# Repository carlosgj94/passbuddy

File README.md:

# Passbuddy — Hardware KeePass for ESP32-S3

Passbuddy is a no_std Rust firmware for the ESP32-S3 that acts like a USB keyboard (HID) to auto-type passwords stored in an on-device KeePass database. The database lives in flash and is encrypted with a software key derived from a user PIN plus the chip’s efuse keyslot 0 (unreadable externally), so secrets never leave the device.

## How It Works
- **Key derivation:** User PIN + IFUSE/HMAC using keyslot 0 → one-time KDF output (software key). The hardware root key never leaves the chip, and the PIN never leaves the device. The software key encrypts/decrypts the KeePass DB.
- **Usage model:** Plug the device; it enumerates as a USB keyboard. Enter PIN locally (buttons/rotary/etc). The DB decrypts on-device. When a login field is focused, the device types the selected password over USB keystrokes.
- **Security posture:** No cloud or sync. Flash theft is useless without the PIN and bypassing S3 anti-dump protections. Vendor compromise is irrelevant because secrets stay on hardware.

## Project Layout
- `src/bin/main.rs` — ESP-RTOS entrypoint; sets CPU clocks, HMAC peripheral, SPI2, and SSD1309 display; draws a simple `ratatui` list via `mousefood`; logs a heartbeat.
- `src/display.rs` — display helpers (`init_terminal`, `initial_state`, `draw_menu`).
- `src/display/ssd1309.rs` — SSD1309 SPI driver implementing `embedded-graphics` `DrawTarget` + framebuffer flush.
- `src/encryption.rs` — HMAC-based software key derivation (`derive_sw_key`).
- `build.rs` — adds linker scripts (`defmt.x`, `linkall.x`) and prints hints for missing symbols.
- `.cargo/config.toml` — targets `xtensa-esp32s3-none-elf`, sets `espflash` runner, enables `build-std` for `core`/`alloc`.

## Prereqs
- Rust toolchain channel `esp` (see `rust-toolchain.toml`); install Xtensa support via Espressif’s toolchain (e.g., `espup`).
- `espflash` installed and USB permissions set (dialout/uaccess on Linux).

## Build, Flash, and Dev
```bash
cargo build                 # dev build for ESP32-S3
cargo build --release       # size-optimized
cargo clippy --no-deps      # lint; keep warnings at zero
cargo run                   # flash + defmt monitor via espflash (device attached)
```
Notes: ensure only one serial/monitor session is open when flashing; replug USB if flashing stalls.

## Architecture Notes
- No_std + Embassy executor; heap set via `esp_alloc::heap_allocator!` in `main`.
- Display: SSD1309 over SPI2 (custom driver); UI rendered with `ratatui`/`mousefood`.
- HID keyboard output planned for password typing; input hardware for PIN entry is TBD.

## Status / Next Steps
- ✅ Display init and static menu render.
- ✅ Software key derivation helper using HMAC + RNG.
- ⏳ Implement PIN input, KeePass DB storage/crypto flow, HID keyboard typing, and runtime UI updates (via Embassy task).

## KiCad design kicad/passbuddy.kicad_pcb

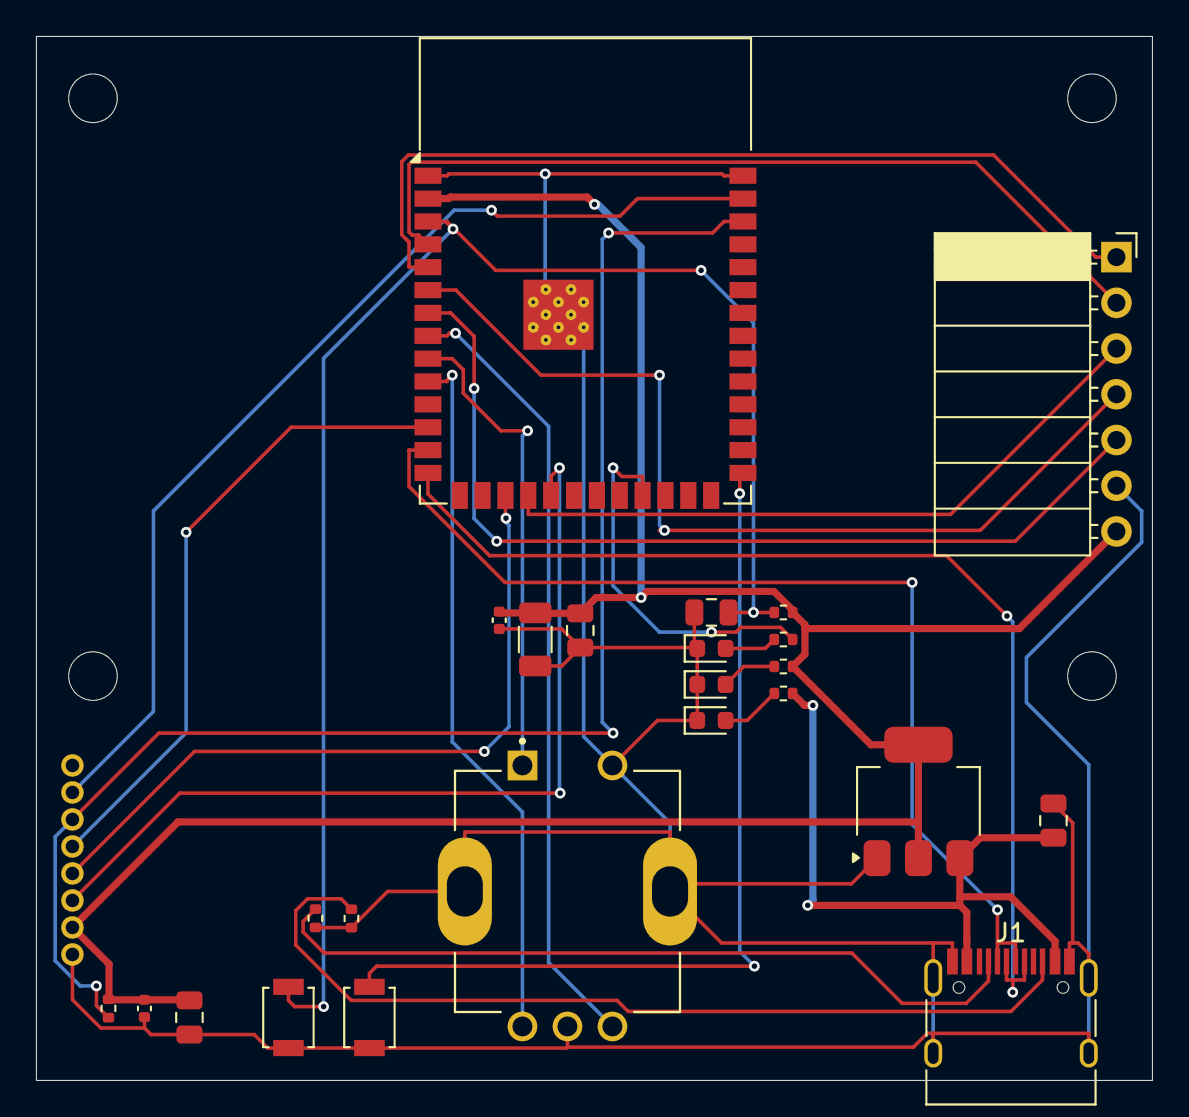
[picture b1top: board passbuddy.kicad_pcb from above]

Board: 2 copper layers, 62.0 x 58.0 mm, 29 parts (0 on the bottom side), 26 nets.

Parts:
C1, C4, C5: 10uF 0805; C_0805_2012Metric
C2: 22uF 1206; C_1206_3216Metric
C3, C6: 100nF 0402; C_0402_1005Metric
C7: 4.7uF 0805; C_0805_2012Metric
D1, D2, D3: LED 0603 White; LED_0603_1608Metric
J1: USB_C_Receptacle_USB2.0_16P; USB_C_Receptacle_HRO_TYPE-C-31-M-12
J2: Conn_01x08_Socket; Tropic01_PinSocket
J3: Conn_01x07_Pin; PinSocket_1x07_P2.54mm_Horizontal
MountHole1, MountHole3, MountHole4: MountHole; MountingHole_2.7mm_M2.5
MountHole2: MountingHole_2.7mm_M2.5
R1, R2, R3, R4, R5, R6: 5.1kΩ 0402; R_0402_1005Metric
R7: 10kΩ 0402; R_0402_1005Metric
S1: PEC11R-4220F-S0024; XDCR_PEC11R-4220F-S0024
SW2, SW3: SW_SPST; SW_SPST_B3U-1000P
U1: ESP32-S3-WROOM-1
U2: LD1117S33TR_SOT223; SOT-223-3_TabPin2

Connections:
+3V3: C1.1, C2.1, C3.1, C6.1, C7.1, J2.7, J3.7, R4.2, R6.1, R7.2, U1.2 (3V3), U2.2 (VO)
+5V: C4.1, J1.A4 (VBUS), J1.A9 (VBUS), J1.B4 (VBUS), J1.B9 (VBUS), R5.1, U2.3 (VI)
CLK: J3.4, U1.6 (IO6)
CS: J3.3, U1.18 (IO10)
D+: J1.A6 (D+), J1.B6 (D+), U1.14 (USB_D+)
D-: J1.A7 (D-), J1.B7 (D-), U1.13 (USB_D-)
DC: J3.2, U1.4 (IO4)
DIN: J3.5, U1.7 (IO7)
EN: C5.1, R6.2, SW3.2 (B), U1.3 (EN)
GND: C1.2, C2.2, C3.2, C4.2, C5.2, C6.2, C7.2, D1.1 (K), D2.1 (K), D3.1 (K), J1.A1 (GND), J1.A12 (GND), J1.B1 (GND), J1.B12 (GND), J1.S1 (SHIELD), J2.8, J3.6, R1.2, R2.2, S1.2, S1.C (COM), S1.SH1 (SHIELD), S1.SH2 (SHIELD), SW2.1 (A), SW3.1 (A), U1.1 (GND), U1.40 (GND), U1.41 (GND), U2.1 (GND)
GPIO0: SW2.2 (B), U1.27 (IO0)
GPIO16: S1.1, U1.9 (IO16)
GPIO21: R3.1, U1.23 (IO21)
unnamed: D1.2 (A), R5.2
unnamed: D2.2 (A), R4.1
unnamed: D3.2 (A), R3.2
unnamed: J1.A5 (CC1), R1.1
unnamed: J1.B5 (CC2), R2.1
RST: J3.1, U1.5 (IO5)
RT_CLK: S1.A, U1.10 (IO17)
RT_DT: S1.B, U1.8 (IO15)
TROPIC_CLK: J2.4, U1.12 (IO8)
TROPIC_CS: J2.3, R7.1, U1.38 (IO2)
TROPIC_GPO: J2.2, U1.39 (IO1)
TROPIC_SDI: J2.6, U1.19 (IO11)
TROPIC_SDO: J2.5, U1.17 (IO9)

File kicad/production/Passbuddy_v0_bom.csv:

Designator,Footprint,Quantity,Value,LCSC Part #
"C1, C4, C5",0805,3,10uF 0805,
C2,1206,1,22uF 1206,
"C3, C6",0402,2,100nF 0402,
C7,0805,1,4.7uF 0805,
"D1, D2, D3",0603,3,LED 0603 White,
J1,USB_C_Receptacle_HRO_TYPE-C-31-M-12,1,USB_C_Receptacle_USB2.0_16P,C53207138
J2,Tropic01_PinSocket,1,Conn_01x08_Socket,
J3,PinSocket_1x07_P2.54mm_Horizontal,1,Conn_01x07_Pin,C2897389
"R1, R2, R3, R4, R5, R6",0402,6,5.1kΩ 0402,
R7,0402,1,10kΩ 0402,
S1,XDCR_PEC11R-4220F-S0024,1,PEC11R-4220F-S0024,
"SW2, SW3",SW_SPST_B3U-1000P,2,SW_SPST,C720477
U1,ESP32-S3-WROOM-1,1,ESP32-S3-WROOM-1,C2913202
U2,SOT-223-3_TabPin2,1,LD1117S33TR_SOT223,C6186

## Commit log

2025-12-10 feat: initial commit
2025-12-10 feat: adding the encryption module with its first function
2025-12-10 feat: adding the initial logic for the display
2025-12-10 chore: adding agents.md
2025-12-10 chore: refactored the display functionality
2025-12-10 feat: added the readme
2025-12-10 chore: removing unneeded no_std
2025-12-10 feat: adding the parsing of the headers for keepass
2025-12-11 feat: adding the entry struct for keepass v1
2025-12-11 feat: adding the group struct
2025-12-11 feat: adding the db
2025-12-11 feat: adding the readme for the keepass database file structure
2025-12-11 feat: adding the dma helper for usage on the key generation
2025-12-11 feat: init structs for the storage module
2025-12-11 feat: storage refactor and adding a function to get the offset to the user storage
2025-12-11 feat: added more metadata in the layout
2025-12-11 feat: initializing the OS storage readying
2025-12-11 feat: starting to hook the layout with main
2025-12-12 feat: setting up the storage write up on first boot
2025-12-12 feat: removing writes from read functions
2025-12-12 feat: magic/offset bug
2025-12-12 feat: making the size of the storage layout constant
2025-12-12 fix: keepass types missalignment
2025-12-12 fix: more fixes on the types for the keepass db
2025-12-12 chore: adding logs to check the OS is working correctly
2025-12-12 fix: avoiding busy spining
2025-12-12 feat: starting the kpdb read
2025-12-13 fix: removing the long ass vec
2025-12-13 feat: adding the ssd1309 driver and hooking it up to the tui
2025-12-13 feat: adding the potentiometer as an input
2025-12-13 feat: refactoring a bit the ui and creating the action button in the inputs
2025-12-13 feat: adding more views to the app
2025-12-13 feat: refactoring the state adding it into the AppState
2025-12-14 feat: refactoring the whole app state and rendering of screens
2025-12-15 feat: adding the group decoding and readying
2025-12-15 feat: loading up the keepass ram db
2025-12-15 feat: adding the display of the different groups in the screens and major refactors in the screens
2025-12-16 fix: offset layout and various errors preventing initialization
2025-12-16 feat: starting to write groups into storage
2025-12-16 feat: first iteration of the select entry view
2025-12-16 fix: adding the id of the group when selecting it
2025-12-16 feat: adding the new entry view
2025-12-16 chore: small changes (non important)
2025-12-16 feat: adding the option to create entries as well
2025-12-16 feat: refactoring the offsets
2025-12-16 feat: improving the button responsiveness
2025-12-17 feat: adding the screen for the text input
2025-12-17 feat: hooking up the entry text to the group creation
2025-12-17 fix: setting correctly the numbers of the new entry forms
2025-12-17 feat: hooking the text form to the entry and adding the password automatically as well
2025-12-17 feat: swapping the potentiometer and the button for a rotatory navigator
2025-12-17 feat: refactoring the selectors for the screens
2025-12-17 fix: creating entries in many groups
2025-12-17 feat: adding the view for the entries
2025-12-17 feat: initialization of the usb
2025-12-17 feat: adding the task for the usb
2025-12-17 feat: building the channels to send/read for the usb
2025-12-17 feat: making the typing work
2025-12-17 feat: refactor on the main.rs so the hid typing happens elsewhere
2025-12-17 feat: adding an animation after creating a new entry/group
2025-12-17 feat: adding flashscreen on boot
2025-12-17 feat: adding a better movement on the paragraph input
2025-12-17 feat: making more adjustments on the paragraph for inputing text to have a better UX
2025-12-17 feat: creating the view for the password
2025-12-17 chore: better naming
2025-12-18 chore: removing the icon_id and url from entry and groups as it's not longer needed (can't be fully displayed in the ui)
2025-12-18 feat: increasing the amount of entries to 256
2026-01-02 feat: realigning the rotatory inputs
2026-01-02 feat: improving the responsiveness of the input
2026-01-02 feat: adding more characterers
2026-01-06 feat: adding the option to delete entries
2026-01-06 feat: disabling autowipeing the storage on boot
2026-01-06 feat: removing the option to add a pin to the group
2026-01-06 feat: adding the screeen to input the pin
2026-02-16 feat: adding the kicad files
